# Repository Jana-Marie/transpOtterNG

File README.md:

# TranspOtterNG

Next Generation of TranspOtter.

[Firmware](https://github.com/NiklasFauth/hoverboard-firmware-hack/tree/transpotter)

[Generation 1](https://github.com/NiklasFauth/hoverboard-firmware-hack/wiki/Build-Instruction:-TranspOtter)

## Libs

https://github.com/Jana-Marie/KiCAD-libs

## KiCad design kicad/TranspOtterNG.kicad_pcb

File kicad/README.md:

# Kicad project

This PCB will connect the mainboard to the Nunchuck, Gametrak and the Display.
Also it will provide 5V and 3.3V as well as the emergency stop.

## To do:

 - Add ESP and RFM69
 - Fit connectors
 - Check size
 - Add an Otter

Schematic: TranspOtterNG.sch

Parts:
AE1: Antenna; Pin_D1.0mm_L10.0mm
C1, C2, C3, C10, C13: 100n; C_0603_1608Metric
C4: 1u; C_0805_2012Metric
C5, C6, C7, C8: 10n; C_0603_1608Metric
C9, C12: 20u; CP_Elec_5x5.3
C14: C_Small; C_0603_1608Metric
D1: 12V; D_SOD-323
D3: LED; LED_0805_2012Metric
J1: UART/I2C; JST_XH_B04B-XH-A_1x04_P2.50mm_Vertical
J2: UART/IO/ANALOG; JST_XH_B04B-XH-A_1x04_P2.50mm_Vertical
J3: Conn_01x04_Male; PinHeader_1x04_P2.54mm_Vertical
J4: GameTrak; PinHeader_1x04_P2.54mm_Vertical
J7: xt30; XT60_angle
J8: Conn_01x05_Male; PinHeader_1x05_P2.54mm_Vertical
J9: Conn_01x16_Female; PinHeader_1x16_P2.54mm_Vertical
MH1, MH2, MH3, MH4: MountingHole; MountingHole_3.2mm_M3
P1: CONN_WII
Q1: Q_NMOS_GDS; SOT-23
Q2: Q_PMOS_GDS; TO-252-2
R1: 470; R_0603_1608Metric
R2, R3: 3k3; R_0603_1608Metric
R4, R5, R6, R7: 1k; R_0603_1608Metric
R8, R9, R21, R22, R23: DNP; R_0603_1608Metric
R10, R11, R12, R13, R14, R18, R19, R20, R27, R28: 10k; R_0603_1608Metric
R15, R16, R17: 100k; R_0603_1608Metric
R26: 220; R_0603_1608Metric
SW1: Flash; SW_DIP_SPSTx01_Slide_Copal_CHS-01A_W5.08mm_P1.27mm_JPin
SW2: Reset; SW_DIP_SPSTx01_Slide_Copal_CHS-01A_W5.08mm_P1.27mm_JPin
U1: AMS1117; SOT-223-3_TabPin2
U2: URB4805YMD-6WR3
U3: RFM69HCW; HOPERF_RFM69HW
U4: ESP-12E
U5: PCF8574; SOIC-16W_7.5x10.3mm_P1.27mm

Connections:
+5V: C2.1, C10.1, C12.1, J3.4, J9.2, J9.15, R18.1, R19.1, R20.1, R27.2, U1.3 (VI), U2.3, U5.16
+15V: J1.1, R15.1
A0: R18.2, R21.2, U5.1
A1: R19.2, R22.2, U5.2
A2: R20.2, R23.2, U5.3
ANT: C14.2, U3.9 (ANT)
CS: J9.6, U5.6
DB4: J9.11, U5.9
DB5: J9.12, U5.10
DB6: J9.13, U5.11
DB7: J9.14, U5.12
GND: C1.2, C2.2, C3.2, C4.2, C5.2, C6.2, C7.2, C8.2, C9.2, C10.2, C12.2, C13.2, J1.4, J2.4, J3.1, J4.1, J7.1, J8.4, J9.1, P1.6, Q1.2, R1.2, R8.2, R9.2, R10.2, R16.2, R21.1, R22.1, R23.1, R26.1, R28.1, SW1.1, SW2.1, U1.1 (ADJ), U2.1, U2.5, U3.1 (GND), U3.8 (GND), U3.10 (GND), U4.15, U5.8
GPIO0: R14.2, SW1.2, U4.18
GPIO4: U3.14 (DIO0), U4.19
GPIO5: J8.3, U4.20
LED_K: J9.16, R26.2
MISO: U3.2 (MISO), U4.6
MOSI: U3.3 (MOSI), U4.7
NSS: R10.1, U3.5 (NSS), U4.16
unnamed: AE1.1, C14.1
unnamed: C5.1, J1.2, R4.2
unnamed: C6.1, J2.2, R6.2
unnamed: C7.1, J1.3, R5.2
unnamed: C8.1, J2.3, R7.2
unnamed: C9.1, Q2.2, U2.2
unnamed: C13.1, R12.1, U4.3
unnamed: D1.1, J7.2, Q2.3
unnamed: D1.2, Q2.1, R17.1
unnamed: D3.1, R1.1
unnamed: Q1.1, R15.2, R16.1
unnamed: Q1.3, R17.2
P3: U5.7
RESET: C1.1, R11.2, SW2.2, U4.1
RS: J9.4, U5.4
RW: J9.5, U5.5
RX0_SDA: P1.5, R3.2, R5.1, U5.15
RX1_ADC2: J4.3, R7.1, R8.1
RXD_ESP: J8.2, U4.21
SCK: U3.4 (SCK), U4.5
TX0_SCL: P1.2, R2.2, R4.1, U5.14
TX1_ADC1: J4.2, R6.1, R9.1
TXD_ESP: J8.1, U4.22
VCC: C3.1, C4.1, D3.2, J3.3, J4.4, J8.5, P1.1, R2.1, R3.1, R11.1, R12.2, R13.1, R14.1, U1.2 (VO), U3.13 (3.3V), U4.8
VO: J9.3, R27.1, R28.2
WS2812: J3.2, R13.2, U4.17

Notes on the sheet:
Input
LDO
LED
I2C
ADC
Nunchuk
VCC

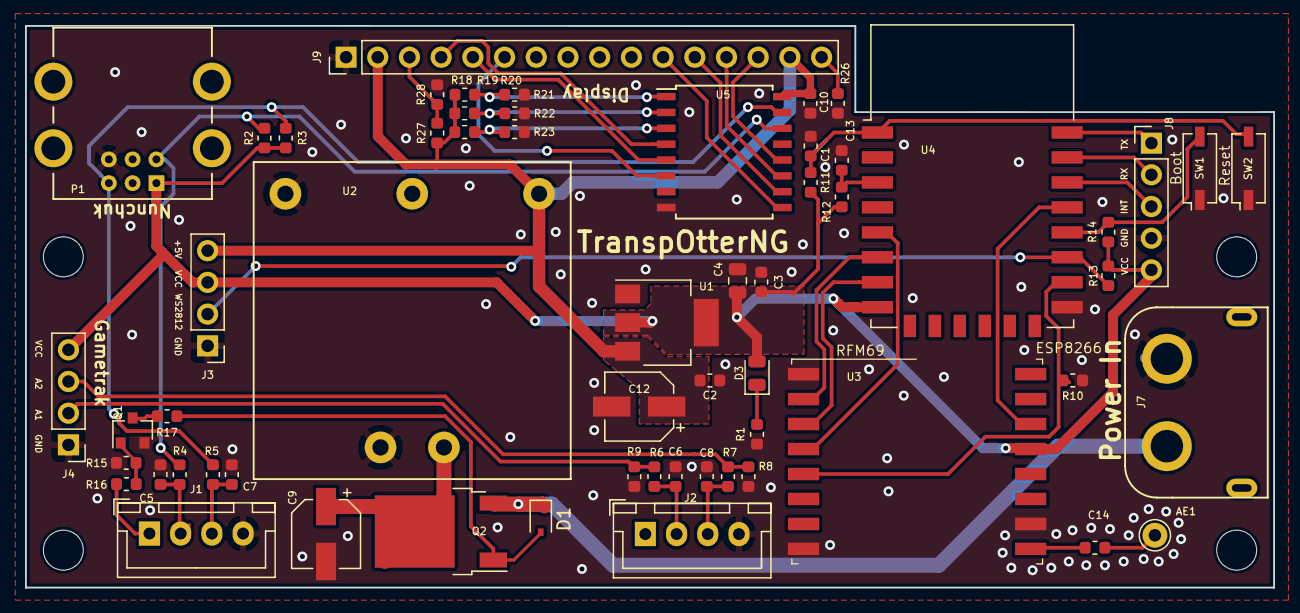
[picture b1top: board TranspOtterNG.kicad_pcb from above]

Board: 2 copper layers, 100.0 x 45.0 mm, 63 parts (0 on the bottom side), 44 nets.

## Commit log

2018-09-19 inital commit
2018-09-19 inital image commit
2018-09-20 changed battery type to F016 L67 804
2018-09-20 update images
2018-09-20 added kicad project
2018-09-20 added kicad/README
2018-09-20 added stepdown
2018-09-20 changed parameters
2018-09-21 added esp and rfm
2018-09-21 added .gitignore
2018-09-24 added programming header
2018-09-26 moved libraries
2018-09-26 update gitignore
2018-10-13 v1 finished
2018-10-13 minor changes, now v2
2018-10-14 minor changes
2018-10-14 added images
2018-10-15 update battery
2018-11-07 fixed file endings
2018-11-08 update scad
2018-11-30 ADD files for transpOtterNG-deluxe
2018-11-30 ADD: pictures
2018-11-30 added image
2018-11-30 ADD: marking of programming interface
2018-11-30 ADD: ST-Link Connection
2018-11-30 renamed images
